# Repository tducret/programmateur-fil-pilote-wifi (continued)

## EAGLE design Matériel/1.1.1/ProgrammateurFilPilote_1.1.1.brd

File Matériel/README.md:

Liste matériel 
==============

BOM File
--------
Vous trouverez la liste du matériel en fonction de la version à l'adresse [suivante][1] (google doc)

[1]: https://docs.google.com/spreadsheets/d/1HEebySHMIzUFYeRYVwTHakMmaWHZ26DxMvw0GtgDD7c

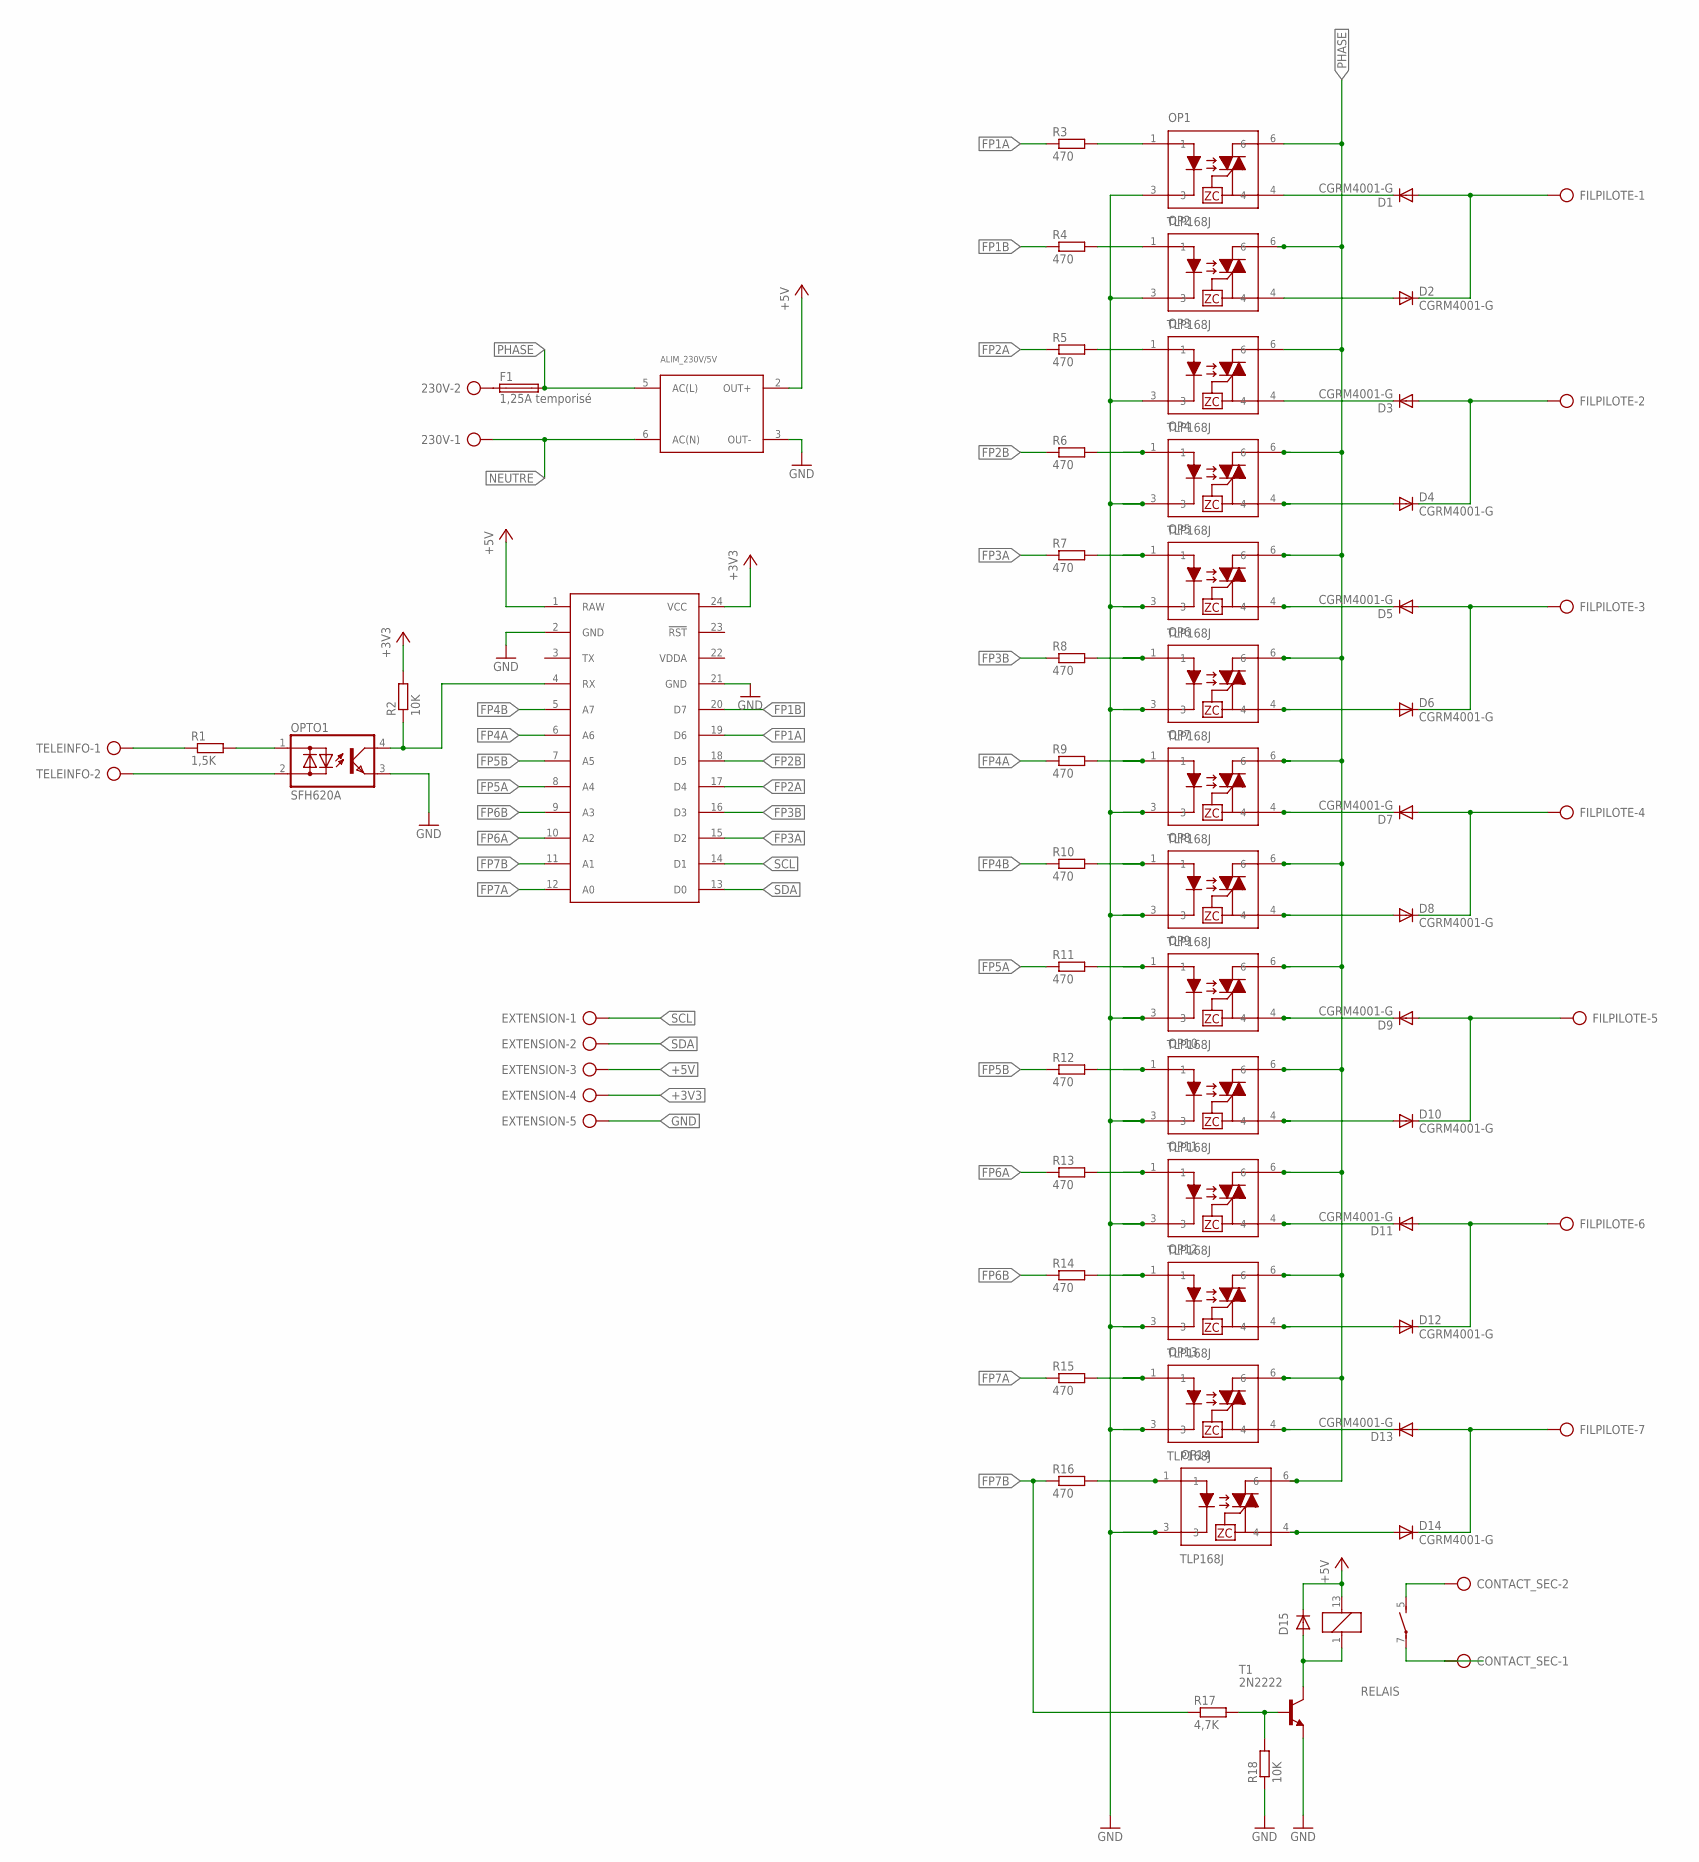
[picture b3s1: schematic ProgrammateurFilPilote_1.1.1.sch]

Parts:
230V: AK500/2
ALIM_230V/5V: TMLM04-SINGLE; TMLM04
CONTACT_SEC: AK500/2
D1, D2, D3, D4, D5, D6, D7, D8, D9, D10, D11, D12, D13, D14, D15: CGRM4001-G; SOD-123_MINI-SMA
EXTENSION: AK500/5
F1: 1,25A temporisé; TE5
FILPILOTE: AK500/7
OP1, OP2, OP3, OP4, OP5, OP6, OP7, OP8, OP9, OP10, OP11, OP12, OP13, OP14: TLP168J; MFSOP-4
OPTO1: SFH620A; DIL04
R1: 1,5K; R1206
R2, R18: 10K; R1206
R3, R4, R5, R6, R7, R8, R9, R10, R11, R12, R13, R14, R15, R16: 470; R1206
R17: 4,7K; R1206
RELAIS: Relais G6D; G6D
SPARKCORE: SPARK_CORECORE; SPARK_CORE
T1: 2N2222; TO92-EBC
TELEINFO: AK500/2

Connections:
+3V3: EXTENSION.4, R2.2, SPARKCORE.24 (VCC)
+5V: ALIM_230V/5V.2 (OUT+), D15.C, EXTENSION.3, RELAIS.13 (2), SPARKCORE.1 (RAW)
FP1A: R3.1, SPARKCORE.19 (D6)
FP1B: R4.1, SPARKCORE.20 (D7)
FP2A: R5.1, SPARKCORE.17 (D4)
FP2B: R6.1, SPARKCORE.18 (D5)
FP3A: R7.1, SPARKCORE.15 (D2)
FP3B: R8.1, SPARKCORE.16 (D3)
FP4A: R9.1, SPARKCORE.6 (A6)
FP4B: R10.1, SPARKCORE.5 (A7)
FP5A: R11.1, SPARKCORE.8 (A4)
FP5B: R12.1, SPARKCORE.7 (A5)
FP6A: R13.1, SPARKCORE.10 (A2)
FP6B: R14.1, SPARKCORE.9 (A3)
FP7A: R15.1, SPARKCORE.12 (A0)
FP7B: R16.1, R17.1, SPARKCORE.11 (A1)
GND: ALIM_230V/5V.3 (OUT-), EXTENSION.5, OP1.3, OP2.3, OP3.3, OP4.3, OP5.3, OP6.3, OP7.3, OP8.3, OP9.3, OP10.3, OP11.3, OP12.3, OP13.3, OP14.3, OPTO1.3 (E), R18.1, SPARKCORE.2 (GND), SPARKCORE.21 (GND), T1.E
unnamed: D1.C, OP1.4
unnamed: D2.A, OP2.4
unnamed: OPTO1.2 (AC2), TELEINFO.2
unnamed: OPTO1.1 (AC1), R1.2
unnamed: R1.1, TELEINFO.1
unnamed: OPTO1.4 (C), R2.1, SPARKCORE.4 (RX)
unnamed: OP1.1, R3.2
unnamed: OP2.1, R4.2
unnamed: OP3.1, R5.2
unnamed: OP4.1, R6.2
unnamed: OP5.1, R7.2
unnamed: OP6.1, R8.2
unnamed: OP7.1, R9.2
unnamed: OP8.1, R10.2
unnamed: D15.A, RELAIS.1, T1.C
unnamed: 230V.2, F1.1
unnamed: CONTACT_SEC.2, RELAIS.5 (S)
unnamed: OP9.1, R11.2
unnamed: CONTACT_SEC.1, RELAIS.7
unnamed: R17.2, R18.2, T1.B
unnamed: D3.C, OP3.4
unnamed: D3.A, D4.C, FILPILOTE.2
unnamed: D5.C, OP5.4
unnamed: D4.A, OP4.4
unnamed: D7.C, OP7.4
unnamed: D5.A, D6.C, FILPILOTE.3
unnamed: D1.A, D2.C, FILPILOTE.1
unnamed: D6.A, OP6.4
unnamed: D7.A, D8.C, FILPILOTE.4
unnamed: D8.A, OP8.4
unnamed: OP10.1, R12.2
unnamed: OP14.1, R16.2
unnamed: D9.C, OP9.4
unnamed: D9.A, D10.C, FILPILOTE.5
unnamed: OP11.1, R13.2
unnamed: OP12.1, R14.2
unnamed: D10.A, OP10.4
unnamed: D11.A, D12.C, FILPILOTE.6
unnamed: D12.A, OP12.4
NEUTRE: 230V.1, ALIM_230V/5V.6 (AC(N))
PHASE: ALIM_230V/5V.5 (AC(L)), F1.2, OP1.6, OP2.6, OP3.6, OP4.6, OP5.6, OP6.6, OP7.6, OP8.6, OP9.6, OP10.6, OP11.6, OP12.6, OP13.6, OP14.6
S$1: D11.C, OP11.4
S$3: D13.C, OP13.4
S$5: OP13.1, R15.2
S$6: D13.A, D14.C, FILPILOTE.7
S$11: D14.A, OP14.4
SCL: EXTENSION.1, SPARKCORE.14 (D1)
SDA: EXTENSION.2, SPARKCORE.13 (D0)
VDDA: SPARKCORE.22 (VDDA)

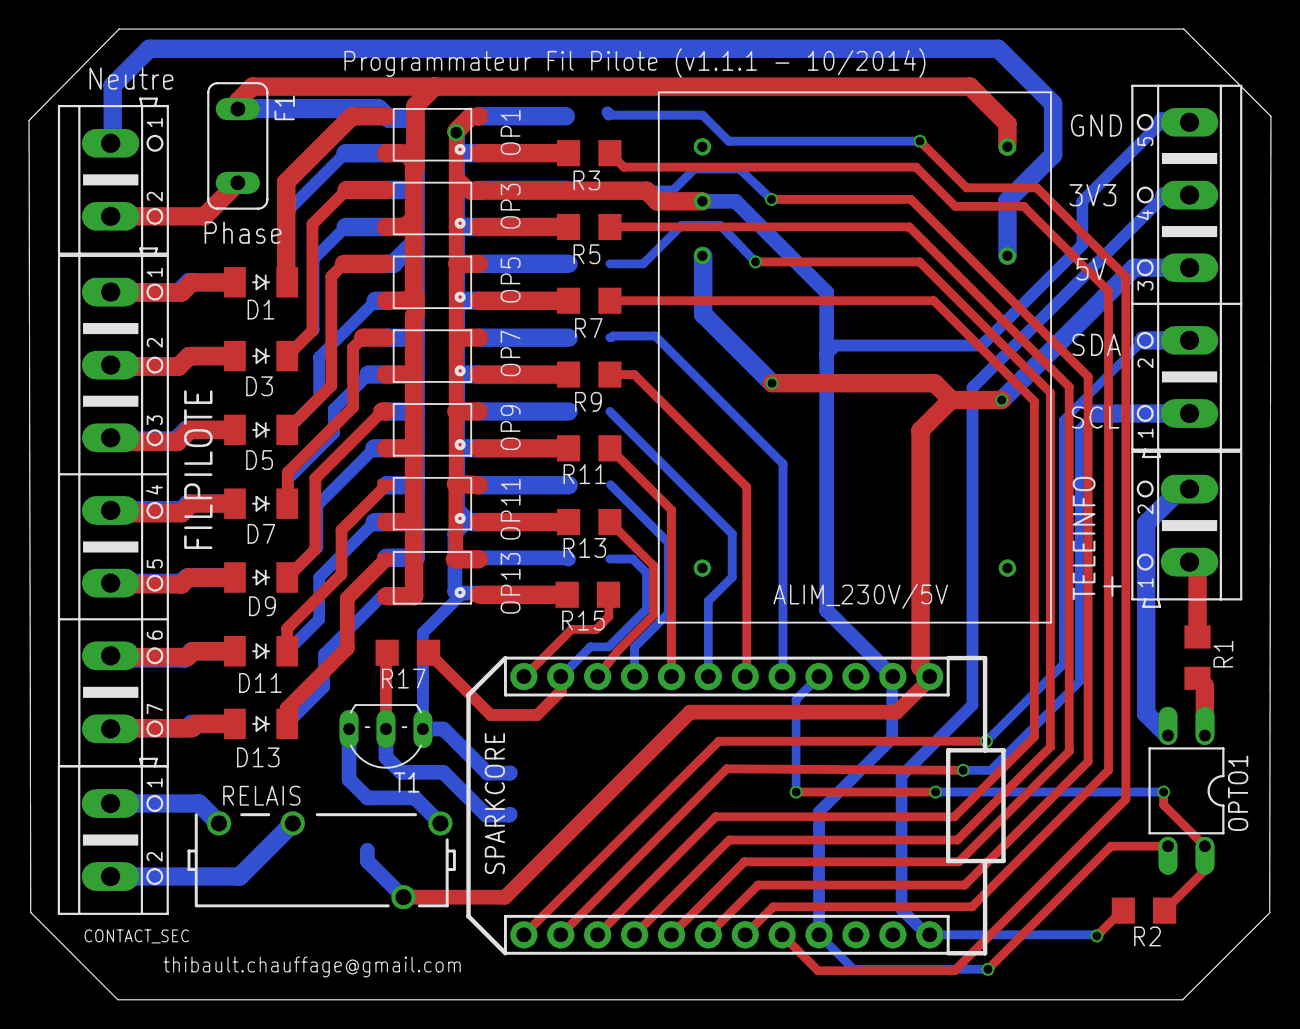
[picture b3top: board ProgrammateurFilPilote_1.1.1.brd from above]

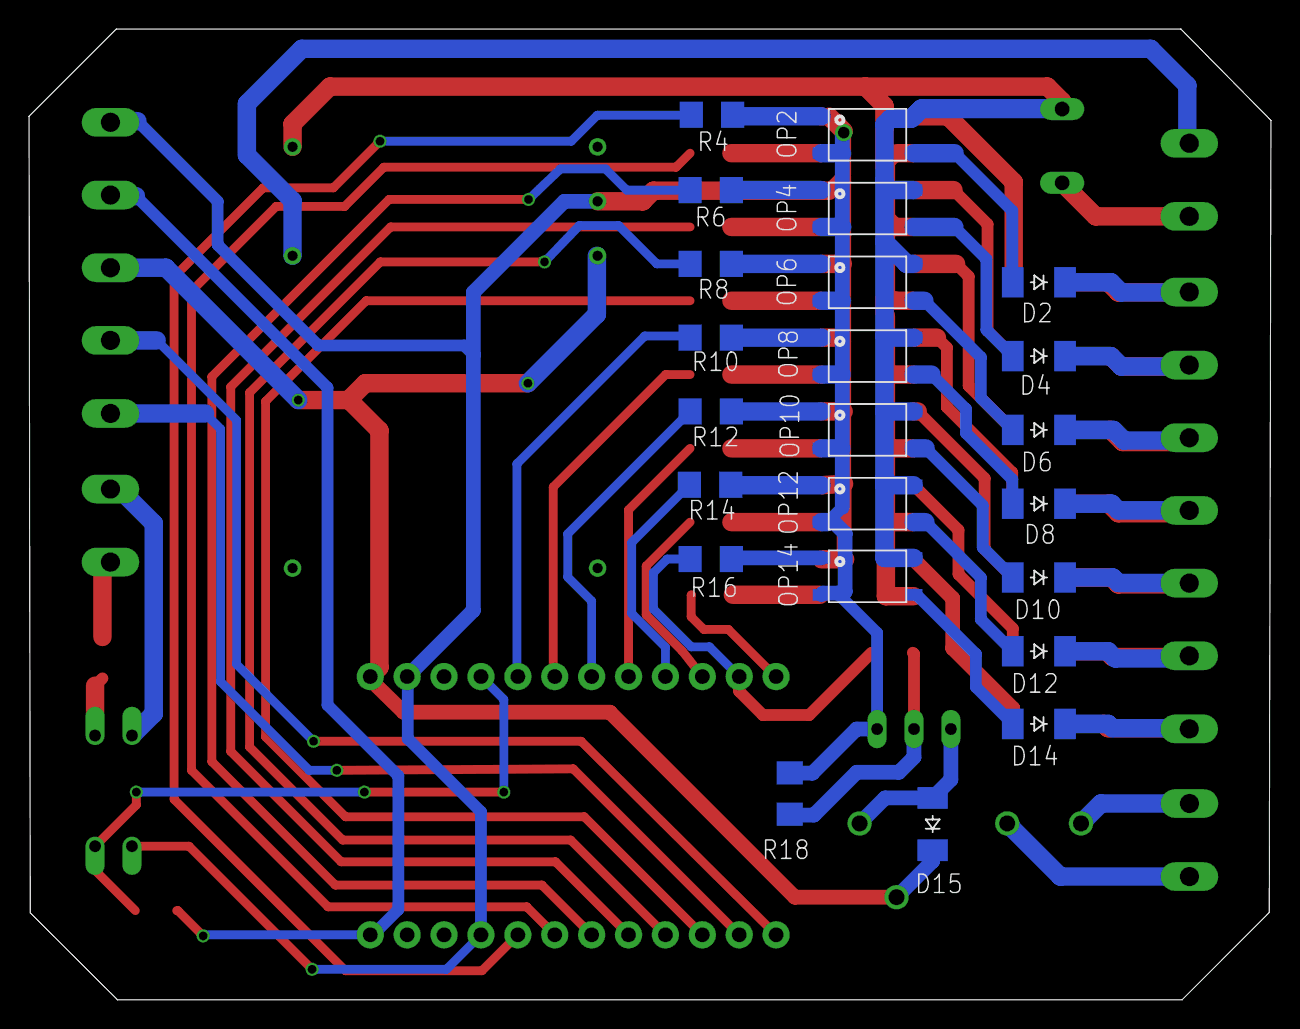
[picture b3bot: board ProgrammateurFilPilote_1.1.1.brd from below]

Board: 2 copper layers, 85.5 x 66.8 mm, 58 parts (23 on the bottom side), 65 nets.

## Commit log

2014-09-29 Ajout du schéma et du routage du programmateur
2014-09-29 Mise à jour Readme
2014-09-29 Ajout du schéma de principe
2014-09-29 Redimension de l'image
2014-10-26 Réorganisation
2014-10-26 Première publication
2014-10-26 Mise à jour des licences utilisées
2014-10-26 Ajout 1.0
2014-10-26 Ajout de la librairie de l'optotriac TLP168J
2014-10-27 Limite de delestage + optimisations
    Calcul automatique de la limite de délestage en fonction de l'intensité
    souscrite
    Suppression du duplicat de code fpControl / fpC
2014-10-29 Ajout de la version 1.1.1
    Ajout d’un fusible 1,25A retardé avant le Traco, et optimisation du
    routage
2014-10-29 Ajout des captures OSHPark
2014-10-29 Ajout des schémas en PDF
2014-11-23 Ajout de la v1.2
    - Ajout d'une extension de ports I2C (16 I/O de plus) => MCP23017
    - Ajout d’un connecteur pour récepteur RF433 (pour le décodage de
    sondes Oregon)
    - Ajout des connexions pour souder une passerelle sans fil (RFM12B,
    RFM69CW ou RFM69HW) + connecteur Antenne U-FL ou fil à souder
    - Ajout connecteur I2C (OLED, ADC externe, … )
2014-11-23 Merge branch 'master' of https://github.com/thibdct/programmateur-fil-pilote-wifi
    Conflicts:
    Logiciel/ProgrammateurFilPilote.ino
2014-12-07 Màj v1.2
2014-12-08 Création
    Création
2014-12-08 Revert "Màj v1.2"
    This reverts commit 1069f649c9f2bcb6078a36c473411e82ae330c49.
2014-12-08 Correction des liens
2014-12-08 Ajout des liens sur les nouveaux composants
2014-12-08 Création
2014-12-08 Ajout de la v1.2
2014-12-08 Suppression
2014-12-08 Suppression du caption
2015-01-05 Ajout du script utilisé avec Jeedom
2015-01-07 Update README.md
    Ajout indication connecteur grove inverse sur le PCB
2015-01-23 Passage en Révision 1.2b
    Correction d'inversion du sens du connecteur Grove
    Correction d'inversion diode D14
2015-01-23 Passage en révision 1.2b
    Correction des erreurs présentes en version 1.2
2015-01-24 Revision 1.2c
2015-01-24 Révision 1.2c
2015-01-27 Ajout Images
2015-01-27 Réduction taille images
2015-01-27 Passage des images à 50%
2015-01-27 Taille images à 45%
2015-01-27 Ajout gestion période tarifaire en cours
2015-01-27 Ajout contrôle de la checksum
2015-01-29 ajout pb de compilation si fichier README.md
2015-01-29 Correction Affichage Bareraph puissance
2015-01-29 Passage du code lié à la téléinfo
    Passage du code lié à la téléinfo dans ce module spécifique pour
    conformité du setup() et loop()
2015-01-29 Ajout compatibilité carte V1.0 et V1.1
    Ajout compatibilité carte V1.0 et V1.1
    Passage code teleinfo dans le module tinfo.cpp
2015-01-29 Ajout visibilité étiquettes ISOUSC et IMAX
2015-01-29 Creation
2015-01-29 Correction bug commande dans fpcontrol
2015-01-29 Correction Status téléinfo
2015-01-29 Erreur de compil si MOD_TELEINFO pas défini
2015-02-14 Nom fonction = nom API exposé
    Renommage fonction fpControl -> fp
    Renommage fonction fsetFP -> setfp
    Afin d'avoir le nom des fonctions internes identiques aux fonctions
    exposées pour une meilleure lisibilité
2015-02-14 8 car max lus par loop
    Récupération que 8 caractères maximum sur la serial par loop, çà peut
    éviter des loop infinis au cas ou
2015-02-14 Gestion reconnexions Cloud
    Redéclaration des variables cloud exposées en cas de perte de connexion
    au cloud.
2015-02-14 MAJ protocol RF pour l'ULPNode
2015-02-15 Création de la fonction de délestage tournant
2015-02-15 l'api setfp peut retourner l'état d'un FP
2015-02-15 Suppression du FP7 sur les cartes V1.0
2015-02-15 Ajout Fonction Delestage
2015-02-15 Suppression des Backup Eagle et Firmware
2015-02-17 Correction d'une regression
    Commande de la mauvaise zone suite à un problème d’index
2015-02-27 Ajout d'information debug au démarrage
2015-02-27 Ajout \n manquant sur info debug teleinfo
2015-03-31 Modifs teleinfos, allinone variable.
2015-04-09 Modifications variables spark Test Ajout client HTTP (non fonctionnel)
2015-04-13 Finalisation ajout variable tinfo
2015-04-13 Ajout variable teleinfo en un seul appel
2015-04-13 ajout retour ligne
2015-04-14 Script initial
2015-04-14 Modification sortie numerique vs alphabetique
2015-04-14 Utilisation de varibales Jeedom
2015-04-14 Ajout varibales Jeedom
2015-09-11 Creation pour compilation correcte
2015-09-11 Revert "Creation pour compilation correcte"
    This reverts commit 39e56a132340877d6f0b19a521f7f4aca1e2624d.
2015-09-11 Suppression erreur compil pour Photon
2015-09-12 Mise à jour suite au passage Spark=>Particle
2015-09-22 Mise à jour de la licence pour le matériel
    Ajout du caractère non commercial (NC) pour que les ressources ne soient pas utilisées pour un but commercial
2015-09-30 ESP8266 / Cloud Variables & Function fix
    Compatibilité ESP8266,
    Intégration de la librairie universelle Téléinfo
    Correction du bug des variables et functions cloud plus exposées avec le
    nouveau firmware sur Spark/Photon
    Mise à plat de tous les fichiers dans le même dossier
2015-09-30 Fix Tabulation
2015-09-30 Erreur de lien
2015-09-30 Correction Compilation ESP8266
2015-09-30 Ajout doc compilation ESP8266
2015-09-30 Ajout OTA
2015-09-30 HeartBeat RBD LED avec la téléinfo
2015-09-30 Correction splash screen
2015-09-30 Dynamic Heartbeat
2015-09-30 Heartbeat si pas de Teleinfo
2015-09-30 Ajout Include pour Web IDE
2015-09-30 Ajout linked_list Web IDE
2015-09-30 Correction bug variables cloud
2015-10-01 Intégration RFM69/RadioHead
2015-10-06 Pb compilation WebServer.h
2015-10-06 Correction suite chg firmware
2015-10-07 Description V1.3
2015-10-07 Ajout Serial.flush() pour précision si plantage au boot
2015-10-07 Ajout lien adaptateur NodeMCU
2015-10-21 Ajustements Finaux
    Résistances 390 Ohm pour nouveaux optos Sharp
    Commandes Opto/led via MCP par la masse
    Ajustement des borniers pour boitier rail DIN
2015-11-17 Ajout d'une ébauche du tutoriel d'assemblage kit Remora v1.3
2015-11-17 Corrections mineures
2015-11-17 La version html n'est pas nécessaire
2015-12-02 Quelques màj suite au premier assemblage
2015-12-06 Mise à jour importante du tutoriel d'assemblage
2015-12-08 Ajout lien logiciel et astuce soudure
2015-12-08 Ajout video soudure
2015-12-24 Ajout photos PCB
2015-12-24 Ajout lien passage optos en 3.3V
2015-12-24 Correction orthographe
2016-01-04 Correction "6 borniers 2 points" => "5 borniers 2 points"
2016-07-24 Ajout implémentation des modes Confort-1 et Confort-2
2016-07-26 Fix typo
2016-07-26 fix typo bis
2016-07-27 Ajout support ESP8266 (compilé avec arduino mais non testé - je n'ai pas d'ESP8266)
2016-08-09 Suppression du _yield() dans le timer. Provoque des interblocages sur particle pour cause d'appel concurrent de Particle.process().
2018-11-12 Mise à jour pour Particle (firmware 0.7.0)
